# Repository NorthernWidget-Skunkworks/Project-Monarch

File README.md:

# Project-Monarch
Designs for a small scale and low cost pyronometer operating in both the short wave and long wave spectral regions

## Millable components

* [Pipe mount](https://easel.inventables.com/projects/cAirZefIUws53oghGYYopw). Accepts 1.25" to 3.25" innner diameter (ID) 1/4" (bolt diameter) U bolts. (1 1/8" U bolts are possible if you're willing to bend them.) Typical sizes available in the USA are 1.25", 1.5", 1.75", and 2".
* [Drilling jig](https://easel.inventables.com/projects/s-fOn9DWTmkeizO0vO8MGw) for Monarch box`

<br>
<br />This work is licensed under a <a rel="license" href="http://creativecommons.org/licenses/by-sa/4.0/">Creative Commons Attribution-ShareAlike 4.0 International License</a>.

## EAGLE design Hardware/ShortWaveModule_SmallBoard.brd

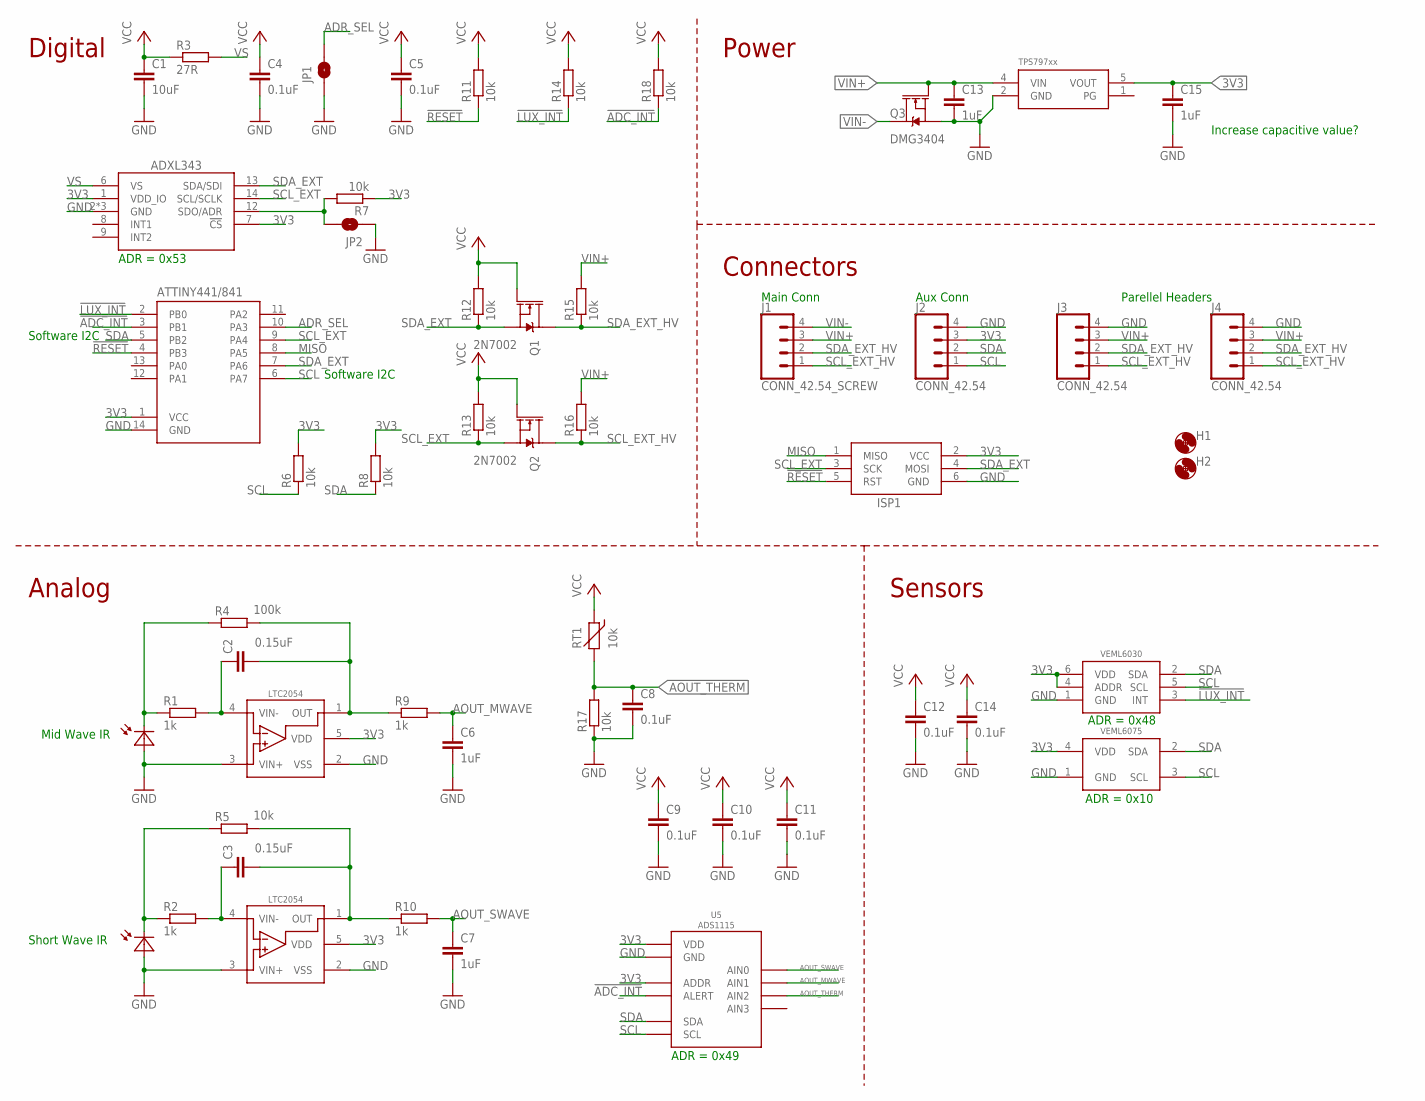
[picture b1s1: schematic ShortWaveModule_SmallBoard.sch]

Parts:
C1: 10uF; C0805
C2, C3: 0.15uF; C0603
C4, C5, C8, C9, C10, C11, C12, C14: 0.1uF; C0603
C6, C7, C13, C15: 1uF; C0603
D1: PHOTODIODESD003-151-001; D1206
D2: PHOTODIODEVEMD1060; D0805
H1, H2: MOUNTING_HOLE4_NP; 4_40
ISP1: AVRISP-6; AVRISP
J1: CONN_42.54_SCREW; 1X04_SCREW
J2, J3, J4: CONN_42.54; 1X04
JP1, JP2: JUMPER-SMT_2_NO_SILK; SMT-JUMPER_2_NO_SILK
Q1, Q2: 2N7002; SOT323
Q3: DMG3404; SOT23-3
R1, R2, R9, R10: 1k; R0603
R3: 27R; R0603
R4: 100k; R0603
R5, R6, R7, R8, R11, R12, R13, R14, R15, R16, R18: 10k; R0603
R17: 10k; R0603; MPN ERA-3AEB103V; DIGIKEY P10KDBCT-ND
RT1: 10k; R0603
U1: ADXL343; LGA-14
U2: ATTINY441/841841; SOIC_14
U3, U4: LTC2054; SOT23-5
U5: ADS1115; VSSOP_10
U6: TPS79733; DCK_R-PDSO-G5
U7: VEML6030
U8: VEML6075

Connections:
3V3: C1.1, C4.1, C5.1, C9.1, C10.1, C11.1, C12.1, C14.1, C15.1, ISP1.2 (VCC), J2.3, Q1.1 (G), Q2.1 (G), R3.1, R6.2, R7.1, R8.2, R11.2, R12.2, R13.2, R14.2, R18.2, RT1.1 (2), U1.1 (VDD_IO), U1.7 (!CS), U2.1 (VCC), U3.5 (VDD), U4.5 (VDD), U5.1 (ADDR), U5.8 (VDD), U6.5 (VOUT), U7.4 (ADDR), U7.6 (VDD), U8.4 (VDD)
!ADC_INT: R18.1, U2.3 (PB1), U5.2 (ALERT)
!LUX_INT: R14.1, U2.2 (PB0), U7.3 (INT)
!RESET: ISP1.5 (RST), R11.1, U2.4 (PB3)
ADR_SEL: JP1.2, U2.10 (PA3)
AOUT_MWAVE: C6.1, R9.2, U5.5 (AIN1)
AOUT_SWAVE: C7.1, R10.2, U5.4 (AIN0)
AOUT_THERM: C8.1, R17.2, RT1.2 (1), U5.6 (AIN2)
GND: C1.2, C4.2, C5.2, C6.2, C7.2, C8.2, C9.2, C10.2, C11.2, C12.2, C13.2, C14.2, C15.2, D1.A, D2.A, ISP1.6 (GND), J2.4, J3.4, J4.4, JP1.1, JP2.1, Q3.2 (S), R17.1, U1.2 (GND), U1.4 (GND), U1.5 (GND), U2.14 (GND), U3.2 (VSS), U3.3 (VIN+), U4.2 (VSS), U4.3 (VIN+), U5.3 (GND), U6.2 (GND), U7.1 (GND), U8.1 (GND)
MISO: ISP1.1 (MISO), U2.8 (PA5)
unnamed: JP2.2, R7.2, U1.12 (SDO/ADR)
unnamed: C3.1, R2.2, U4.4 (VIN-)
unnamed: D2.C, R2.1, R5.1
unnamed: D1.C, R1.1, R4.1
unnamed: C2.1, R1.2, U3.4 (VIN-)
unnamed: C2.2, R4.2, R9.1, U3.1 (OUT)
unnamed: C3.2, R5.2, R10.1, U4.1 (OUT)
SCL: J2.1, R6.1, U2.6 (PA7), U5.10 (SCL), U7.5 (SCL), U8.3 (SCL)
SCL_EXT: ISP1.3 (SCK), Q2.2 (S), R13.1, U1.14 (SCL/SCLK), U2.9 (PA4)
SCL_EXT_HV: J1.1, J3.1, J4.1, Q2.3 (D), R16.1
SDA: J2.2, R8.1, U2.5 (PB2), U5.9 (SDA), U7.2 (SDA), U8.2 (SDA)
SDA_EXT: ISP1.4 (MOSI), Q1.2 (S), R12.1, U1.13 (SDA/SDI), U2.7 (PA6)
SDA_EXT_HV: J1.2, J3.2, J4.2, Q1.3 (D), R15.1
VIN+: C13.1, J1.3, J3.3, J4.3, Q3.1 (G), R15.2, R16.2, U6.4 (VIN)
VIN-: J1.4, Q3.3 (D)
VS: R3.2, U1.6 (VS)

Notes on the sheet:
Software I2C
ADR = 0x48
ADR = 0x10
ADR = 0x49
Increase capacitive value?
Digital
Sensors
Power
Analog
Short Wave IR
Mid Wave IR
Connectors
Main Conn
Aux Conn
Parellel Headers
ADR = 0x53

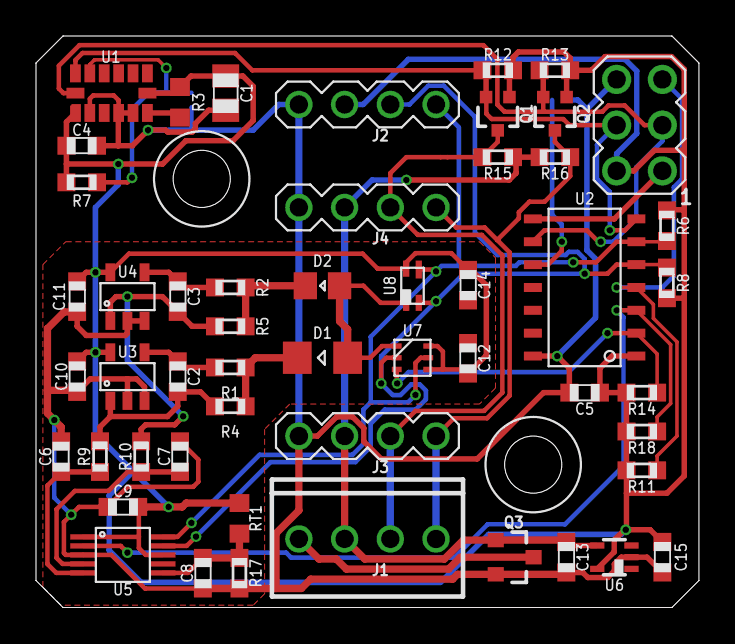
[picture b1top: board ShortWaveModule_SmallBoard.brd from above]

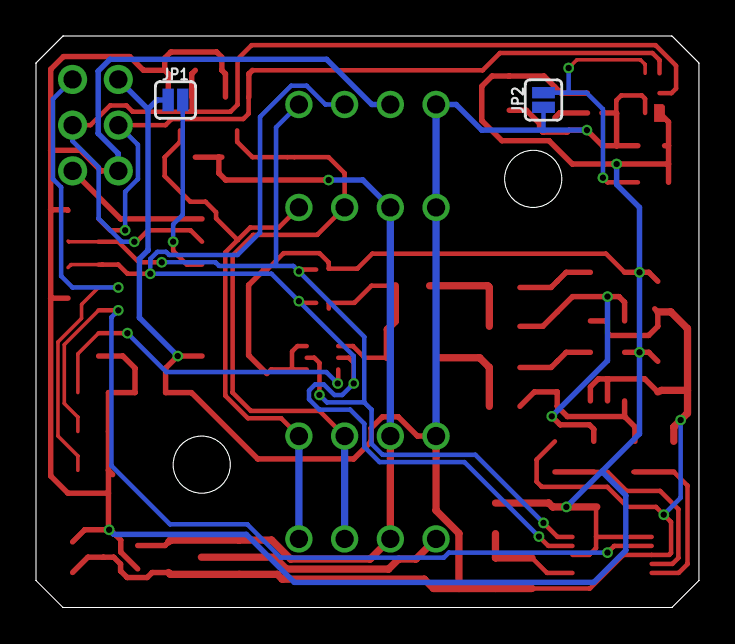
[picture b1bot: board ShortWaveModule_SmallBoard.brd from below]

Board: 2 copper layers, 36.8 x 31.8 mm, 56 parts (2 on the bottom side), 26 nets.

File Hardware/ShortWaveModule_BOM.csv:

"Qty","Value","Device","Package","Parts","Description","DIGIKEY","DISP","MF","MPN","PROD_ID","VALUE","VALUE_PART",
"2","","MOUNTING_HOLE4_NP","4_40","H1, H2","Genaric Mechanical Mounting Hole","","","","","","","",
"2","0.15uF","C-EU0.15UFC0603","C0603","C2, C3","CAPACITOR, European symbol","732-7990-1-ND","","Wurth","885012206072","","","",
"8","0.1uF","C-EU0.1UFC0603","C0603","C4, C5, C8, C9, C10, C11, C12, C14","CAPACITOR, European symbol","490-6051-1-ND","","Murata","GCM188R71E104KA57D","","","",
"1","100k","R-EU_P100KR0603","R0603","R4","RESISTOR, European symbol","P100KDBCT-ND","","Panasonic","ERA-3AEB104V","","","100k",
"10","10k","R-EU_10KR0603","R0603","R6, R7, R8, R11, R12, R13, R14, R15, R16, R18","RESISTOR, European symbol","P10.0KHCT-ND","","Panasonic","ERJ-3EKF1002V","","","10k",
"1","10k","R-EU_P10KR0603","R0603","R17","RESISTOR, European symbol","P10KDBCT-ND","","Panasonic ","ERA-3AEB103V","","","10k",
"1","10k","R-EU_P10KR0603","R0603","R5","RESISTOR, European symbol","P10KDBCT-ND","","Panasonic","ERA-3AEB103V","","","10k",
"1","10k","THERMISTOR10K","R0603","RT1","Thermistor","490-16279-1-ND","","Murata","NCU18XH103F60RB","","","",
"1","10uF","C-EU10UFC0805","C0805","C1","CAPACITOR, European symbol","490-6473-6-ND","","Murata","GRM21BR61C106KE15K","","","",
"4","1k","R-EU_P1KR0603","R0603","R1, R2, R9, R10","RESISTOR, European symbol","P1.0KDBCT-ND","","Panasonic","ERA-3AEB102V","","","1k",
"4","1uF","C-EU1UFC0603","C0603","C6, C7, C13, C15","CAPACITOR, European symbol","1276-6524-1-ND","","Samsung","1276-6524-1-ND","","","",
"1","27R","R-EU_27R0603","R0603","R3","RESISTOR, European symbol","311-27.0HRCT-ND","","Yageo","RC0603FR-0727RL","","","27",
"2","2N7002","MOSFET-NCH-2N7002PW","SOT323","Q1, Q2","N-channel MOSFETs","2N7002W-FDICT-ND","","Diodes Incorporated","2N7002W-7-F","TRANS-11151","2N7002","",
"1","ADS1115","ADS1115","VSSOP_10","U5","ADS1115 - Sigma Delta ADC","296-38849-1-ND","","TI","ADS1115IDGSR","","","",
"1","ADXL343","ADXL343","LGA-14","U1","ADXL343 - Digital Accelerometer(I2C/SPI)","ADXL343BCCZ-ND","","Analog Devices","ADXL343BCCZ","","","",
"1","ATTINY441/841841","ATTINY441/841841","SOIC_14","U2","ATTINY441, ATTINY841 8 bit MCU, 4/8k flash, 256/512B SRAM","ATTINY841-SSU-ND","","Atmel","ATTINY841-SSU","","","",
"1","AVRISP-6","AVRISP-6","AVRISP","ISP1","AVR ISP HEADER","","","","","","","",
"3","CONN_42.54","CONN_42.54","1X04","J2, J3, J4","Genaric 4 pin connector","","","","","","","",
"1","CONN_42.54_SCREW","CONN_42.54_SCREW","1X04_SCREW","J1","Genaric 4 pin connector","ED10563-ND","","On Shore","OSTVN04A150","","","",
"1","DMG3404","MOSFET-NCH-DMG3404L","SOT23-3","Q3","N-channel MOSFETs","DMG3404L-7DICT-ND","","Diodes Incorporated","DMG3404L-7","","DMG3404","",
"2","JUMPER-SMT_2_NO_SILK","JUMPER-SMT_2_NO_SILK","SMT-JUMPER_2_NO_SILK","JP1, JP2","Normally open jumper","","","","","","","",
"2","LTC2054","LTC2054","SOT23-5","U3, U4","LTC2054 -Single Micropower Zero Drift Op-Amp","LTC2054HS5#TRMPBFCT-ND","LTC2054","LT","LTC2054HS5#TRMPBF","","","",
"1","PHOTODIODESD003-151-001","PHOTODIODESD003-151-001","D1206","D1","Photodiode","SD003-151-001CT-ND","","Luna Opto","SD003-151-001","","","",
"1","PHOTODIODEVEMD1060","PHOTODIODEVEMD1060","D0805","D2","Photodiode","VEMD1060X01CT-ND ","","Vishay","VEMD1060X01","","","",
"1","TPS79733","TPS79733","DCK_R-PDSO-G5","U6","TPS797xx, Ultra low power linear voltage regulator, fixed voltages of 1.8v, 3v, 3.3v","296-11990-1-ND","","TI","TPS79733DCKR","","","",
"1","VEML6030","VEML6030","VEML6030","U7","VEML6030 - Ambient Light Sensor with I2C Interface","VEML6030-GS15CT-ND","","Vishay","VEML6030-GS15","","","",
"1","VEML6075","VEML6075","VEML6075","U8","VEML6075 - UVA and UVB Light Sensor with I2C Interface","VEML6075CT-ND","","Vishay","VEML6075","","","",

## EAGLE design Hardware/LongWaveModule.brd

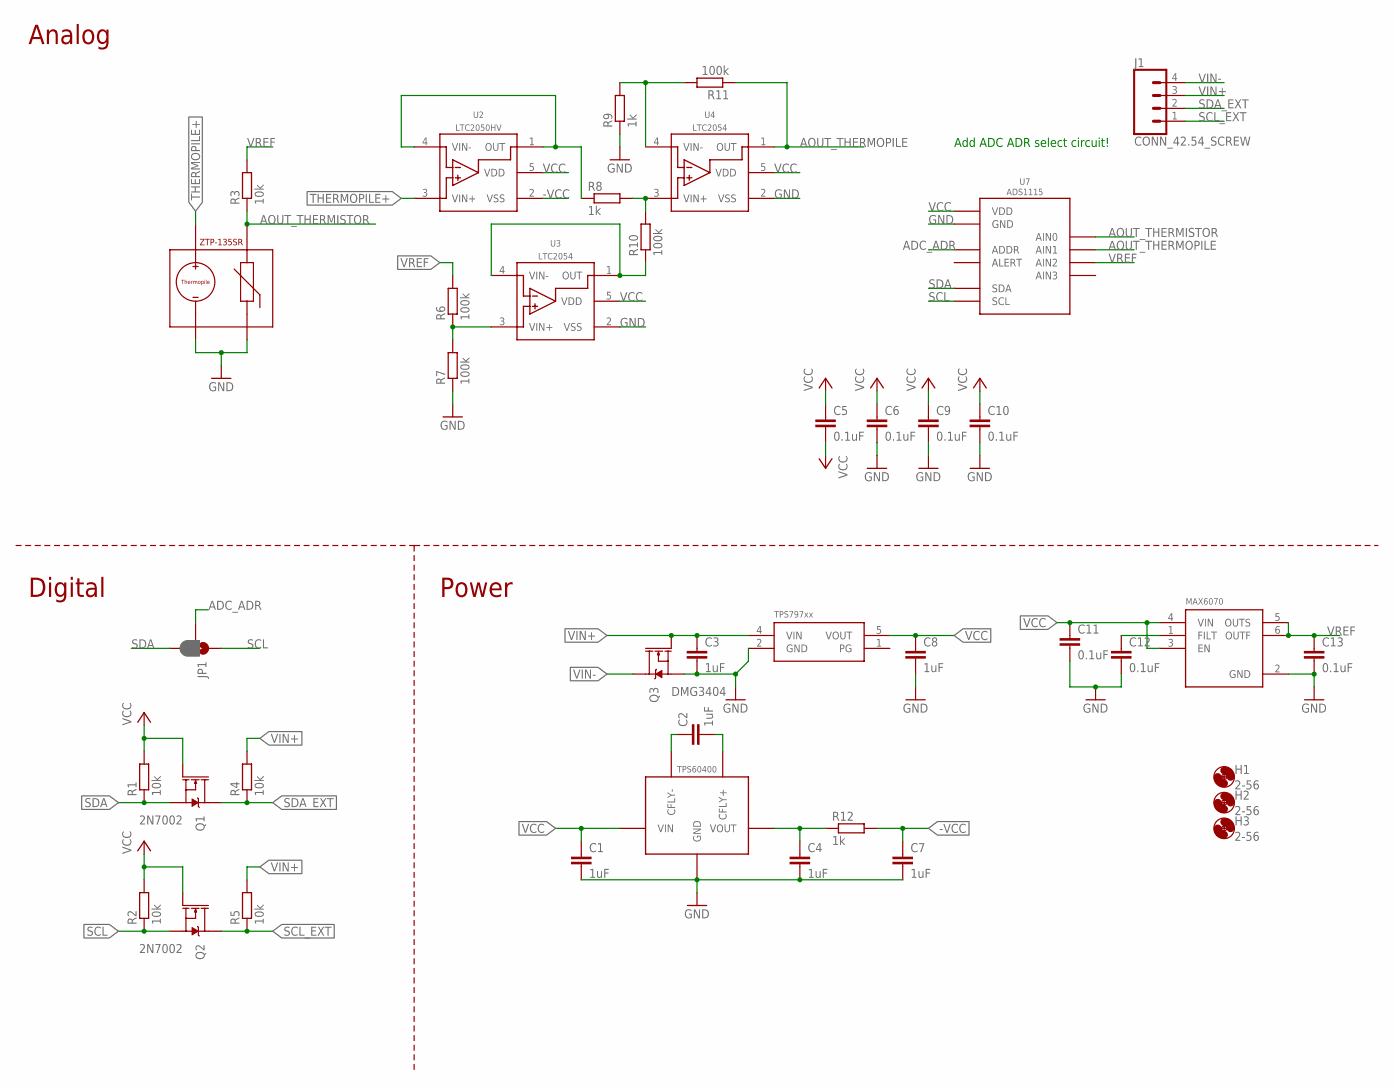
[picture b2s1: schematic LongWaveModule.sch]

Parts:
C1, C2, C3, C4, C7, C8: 1uF; C0603
C5, C6, C9, C10, C11, C12, C13: 0.1uF; C0603
H1, H2, H3: 2-56; 2_56
J1: CONN_42.54_SCREW; 1X04_SCREW
JP1: JUMPER-SMT_3_1-NC_PASTE_SILK; SMT-JUMPER_3_1-NC_PASTE_SILK
Q1, Q2: 2N7002; SOT323
Q3: DMG3404; SOT23-3
R1, R2, R3, R4, R5: 10k; R0603
R6, R7, R10, R11: 100k; R0603
R8, R9, R12: 1k; R0603
U1: STP-135SR; TO-46
U2: LTC2050HV; SOT23-5
U3, U4: LTC2054; SOT23-5
U5: TPS60403; SOT23-5
U6: TPS79733; DCK_R-PDSO-G5
U7: ADS1115; VSSOP_10
U8: MAX6070AAUT18; SOT23-6L

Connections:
-VCC: C5.2, C7.1, R12.2, U2.2 (VSS)
ADC_ADR: JP1.2, U7.1 (ADDR)
AOUT_THERMISTOR: R3.1, U1.THERMISTOR+, U7.4 (AIN0)
AOUT_THERMOPILE: R11.1, U4.1 (OUT), U7.5 (AIN1)
GND: C1.2, C3.2, C4.2, C6.2, C7.2, C8.2, C9.2, C10.2, C11.2, C12.2, C13.2, Q3.2 (S), R7.1, R9.1, U1.THERMISTOR_GND (THERMISTOR-), U1.THERMOPILE_GND (THEMROPILE-), U3.2 (VSS), U4.2 (VSS), U5.4 (GND), U6.2 (GND), U7.3 (GND), U8.2 (GND)
unnamed: R8.1, U2.1 (OUT), U2.4 (VIN-)
unnamed: R8.2, R10.2, U4.3 (VIN+)
unnamed: R9.2, R11.2, U4.4 (VIN-)
unnamed: R10.1, U3.1 (OUT), U3.4 (VIN-)
unnamed: R6.1, R7.2, U3.3 (VIN+)
unnamed: C12.1, U8.1 (FILT)
unnamed: C2.1, U5.3 (CFLY-)
unnamed: C2.2, U5.5 (CFLY+)
unnamed: C4.1, R12.1, U5.1 (VOUT)
SCL: JP1.1, Q2.2 (S), R2.1, U7.10 (SCL)
SCL_EXT: J1.1, Q2.3 (D), R5.1
SDA: JP1.3, Q1.2 (S), R1.1, U7.9 (SDA)
SDA_EXT: J1.2, Q1.3 (D), R4.1
THERMOPILE+: U1.THERMOPILE+, U2.3 (VIN+)
VCC: C1.1, C5.1, C6.1, C8.1, C9.1, C10.1, C11.1, Q1.1 (G), Q2.1 (G), R1.2, R2.2, U2.5 (VDD), U3.5 (VDD), U4.5 (VDD), U5.2 (VIN), U6.5 (VOUT), U7.8 (VDD), U8.3 (EN), U8.4 (VIN)
VIN+: C3.1, J1.3, Q3.1 (G), R4.2, R5.2, U6.4 (VIN)
VIN-: J1.4, Q3.3 (D)
VREF: C13.1, R3.2, R6.2, U7.6 (AIN2), U8.5 (OUTS), U8.6 (OUTF)

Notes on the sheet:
Add ADC ADR select circuit!
Analog
Digital
Power

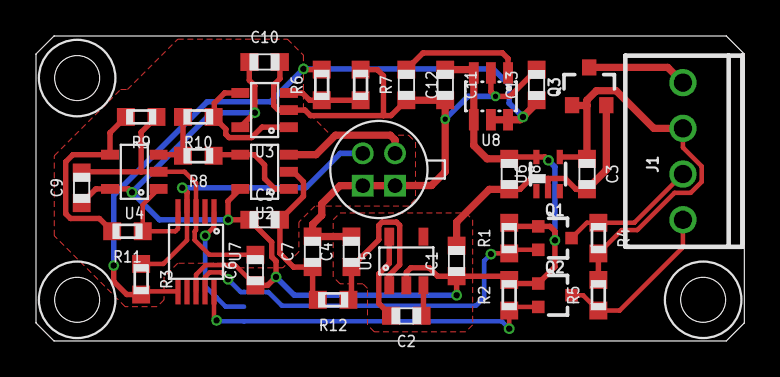
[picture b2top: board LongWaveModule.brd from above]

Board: 2 copper layers, 39.4 x 16.9 mm, 41 parts (1 on the bottom side), 23 nets.

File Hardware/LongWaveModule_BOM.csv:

"Qty","Value","Device","Package","Parts","Description","DIGIKEY","DISP","MF","MPN","PROD_ID","VALUE","VALUE_PART",
"7","0.1uF","C-EU0.1UFC0603","C0603","C5, C6, C9, C10, C11, C12, C13","CAPACITOR, European symbol","490-6051-1-ND","","Murata","GCM188R71E104KA57D","","","",
"4","100k","R-EU_P100KR0603","R0603","R6, R7, R10, R11","RESISTOR, European symbol","P100KDBCT-ND","","Panasonic","ERA-3AEB104V","","","100k",
"4","10k","R-EU_10KR0603","R0603","R1, R2, R4, R5","RESISTOR, European symbol","P10.0KHCT-ND","","Panasonic","ERJ-3EKF1002V","","","10k",
"1","10k","R-EU_P10KR0603","R0603","R3","RESISTOR, European symbol","P10KDBCT-ND","","Panasonic","ERA-3AEB103V","","","10k",
"1","1k","R-EU_1KR0603","R0603","R12","RESISTOR, European symbol","311-1KLDCT-ND","","Yageo","AC0603FR-071KL","","","1k",
"2","1k","R-EU_P1KR0603","R0603","R8, R9","RESISTOR, European symbol","P1.0KDBCT-ND","","Panasonic","ERA-3AEB102V","","","1k",
"6","1uF","C-EU1UFC0603","C0603","C1, C2, C3, C4, C7, C8","CAPACITOR, European symbol","1276-6524-1-ND","","Samsung","1276-6524-1-ND","","","",
"3","2-56","MOUNTING_HOLE2_NP","2_56","H1, H2, H3","Genaric Mechanical Mounting Hole","","","","","","","",
"2","2N7002","MOSFET-NCH-2N7002PW","SOT323","Q1, Q2","N-channel MOSFETs","2N7002W-FDICT-ND","","Diodes Incorporated","2N7002W-7-F","TRANS-11151","2N7002","",
"1","ADS1115","ADS1115","VSSOP_10","U7","ADS1115 - Sigma Delta ADC","296-38849-1-ND","","TI","ADS1115IDGSR","","","",
"1","CONN_42.54_SCREW","CONN_42.54_SCREW","1X04_SCREW","J1","Genaric 4 pin connector","ED10563-ND","","On Shore","OSTVN04A150","","","",
"1","DMG3404","MOSFET-NCH-DMG3404L","SOT23-3","Q3","N-channel MOSFETs","DMG3404L-7DICT-ND","","Diodes Incorporated","DMG3404L-7","","DMG3404","",
"1","JUMPER-SMT_3_1-NC_PASTE_SILK","JUMPER-SMT_3_1-NC_PASTE_SILK","SMT-JUMPER_3_1-NC_PASTE_SILK","JP1","Normally closed solder jumper (1 of 2 connections)","","","","","","","",
"1","LTC2050HV","LTC2050HV","SOT23-5","U2","LTC2050 -Single Micropower Zero Drift Op-Amp","LTC2050HVIS5#TRPBFCT-ND","LTC2050HV","LT","LTC2050HVIS5#TRPBF","","","",
"2","LTC2054","LTC2054","SOT23-5","U3, U4","LTC2054 -Single Micropower Zero Drift Op-Amp","LTC2054HS5#TRMPBFCT-ND","LTC2054","LT","LTC2054HS5#TRMPBF","","","",
"1","MAX6070AAUT18","MAX6070AAUT18","SOT23-6L","U8","MAX6070 Low Noise high precision voltage referance","MAX6070BAUT18+TCT-ND","","Maxim","MAX6070BAUT18+T","","","",
"1","STP-135SR","STP-135SR","TO-46","U1","ZTP-135SR - Thermopile Temp Sensor with integrated thermistor","235-1330-ND","","Amphenol","ZTP-135SR","","","",
"1","TPS60403","TPS60403","SOT23-5","U5","TPS6040x - Unregulated Charge Pump Voltage Inverter","296-27005-1-ND","","TI","TPS60403DBVR","","","",
"1","TPS79733","TPS79733","DCK_R-PDSO-G5","U6","TPS797xx, Ultra low power linear voltage regulator, fixed voltages of 1.8v, 3v, 3.3v","296-11990-1-ND","","TI","TPS79733DCKR","","","",

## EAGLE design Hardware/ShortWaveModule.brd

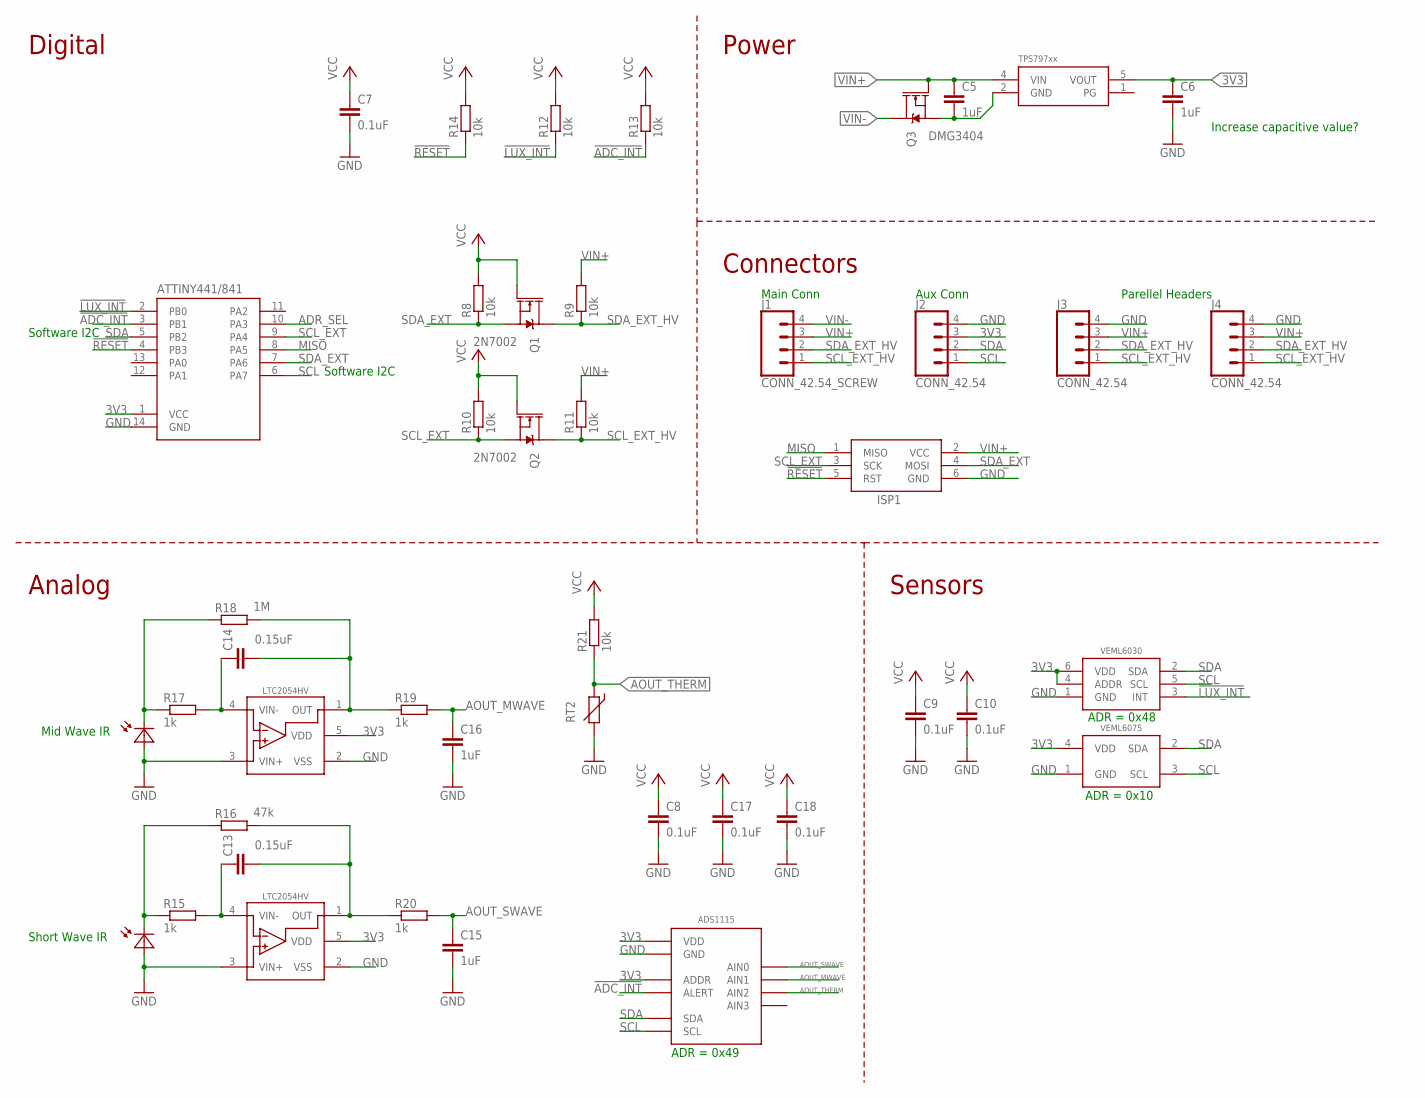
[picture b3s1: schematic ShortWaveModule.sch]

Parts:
ADS1115: ADS1115; VSSOP_10
C5, C6, C15, C16: 1uF; C0603
C7, C8, C9, C10, C17, C18: 0.1uF; C0603
C13, C14: 0.15uF; C0603
ISP1: AVRISP-6; AVRISP
J1: CONN_42.54_SCREW; 1X04_SCREW
J2, J3, J4: CONN_42.54; 1X04
Q1, Q2: 2N7002; SOT323
Q3: DMG3404; SOT23-3
R8, R9, R10, R11, R12, R13, R14, R21: 10k; R0603
R15, R17, R19, R20: 1k; R0603
R16: 47k; R0603
R18: 1M; R0603
RT2: THERMISTOR10K; R0603
U$1: ATTINY441/841841; SOIC_14
U$2: VEML6030
U$3: VEML6075
U$5: TPS79733; DCK_R-PDSO-G5
U$9: PHOTODIODEMTD5010W; TO-18
U$10: PHOTODIODESD003-151-001; D1206
U$11, U$12: LTC2054HV; SOT23-5

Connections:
3V3: ADS1115.1 (ADDR), ADS1115.8 (VDD), C6.1, C7.1, C8.1, C9.1, C10.1, C17.1, C18.1, J2.3, Q1.1 (G), Q2.1 (G), R8.2, R10.2, R12.2, R13.2, R14.2, R21.2, U$1.1 (VCC), U$2.4 (ADDR), U$2.6 (VDD), U$3.4 (VDD), U$5.5 (VOUT), U$11.5 (VDD), U$12.5 (VDD)
!ADC_INT: ADS1115.2 (ALERT), R13.1, U$1.3 (PB1)
!LUX_INT: R12.1, U$1.2 (PB0), U$2.3 (INT)
!RESET: ISP1.5 (RST), R14.1, U$1.4 (PB3)
ADR_SEL: U$1.10 (PA3)
AOUT_MWAVE: ADS1115.5 (AIN1), C14.2, R18.2, R19.1, U$11.1 (OUT)
AOUT_SWAVE: ADS1115.4 (AIN0), C13.2, R16.2, R20.1, U$12.1 (OUT)
AOUT_THERM: ADS1115.6 (AIN2), R21.1, RT2.1
GND: ADS1115.3 (GND), C6.2, C7.2, C8.2, C9.2, C10.2, C15.2, C16.2, C17.2, C18.2, ISP1.6 (GND), J2.4, J3.4, J4.4, RT2.2, U$1.14 (GND), U$2.1 (GND), U$3.1 (GND), U$9.ANODE (A), U$10.A, U$11.2 (VSS), U$11.3 (VIN+), U$12.2 (VSS), U$12.3 (VIN+)
MISO: ISP1.1 (MISO), U$1.8 (PA5)
unnamed: C5.2, Q3.2 (S), U$5.2 (GND)
unnamed: C13.1, R15.2, U$12.4 (VIN-)
unnamed: R15.1, R16.1, U$9.CATHODE (C)
unnamed: R17.1, R18.1, U$10.C
unnamed: C14.1, R17.2, U$11.4 (VIN-)
unnamed: C16.1, R19.2
unnamed: C15.1, R20.2
SCL: ADS1115.10 (SCL), J2.1, U$1.6 (PA7), U$2.5 (SCL), U$3.3 (SCL)
SCL_EXT: ISP1.3 (SCK), Q2.2 (S), R10.1, U$1.9 (PA4)
SCL_EXT_HV: J1.1, J3.1, J4.1, Q2.3 (D), R11.1
SDA: ADS1115.9 (SDA), J2.2, U$1.5 (PB2), U$2.2 (SDA), U$3.2 (SDA)
SDA_EXT: ISP1.4 (MOSI), Q1.2 (S), R8.1, U$1.7 (PA6)
SDA_EXT_HV: J1.2, J3.2, J4.2, Q1.3 (D), R9.1
VIN+: C5.1, ISP1.2 (VCC), J1.3, J3.3, J4.3, Q3.1 (G), R9.2, R11.2, U$5.4 (VIN)
VIN-: J1.4, Q3.3 (D)

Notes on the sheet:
Software I2C
ADR = 0x48
ADR = 0x10
ADR = 0x49
Increase capacitive value?
Digital
Sensors
Power
Analog
Short Wave IR
Mid Wave IR
Connectors
Main Conn
Aux Conn
Parellel Headers

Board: 2 copper layers, 44 parts (0 on the bottom side), 24 nets, no tracks yet.

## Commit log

2018-06-05 Rebuild repo
    Previous repo was borked due to inclusion of large peripheral files from LTSpice simulations, repo is now being rebuild with changes to gitignore in order to prevent issues like this in the future
2018-06-05 Made fixes to #2, #3, #4
    Fixed the silk screen numbering issue, fixed pinout of thermopile, connected voltage ref pin
2018-06-07 Added sub-alpha firmware
    I2C firmware used for translating I2C commands and readdressing (currently not functional), driver firmware is used as a true sensor interface to read from sub-slaves and populate registers (currentl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
2018-06-08 Improved driver files, and demo file
    Driver file in BETA, demo file still in ALPHA
2018-06-12 Updated to driver firmware and demo interface
    Initial design of driver firmware nearly completed, basics of demo interface complete, polishing and boilerplate required
2018-06-13 Firmware and demo interface updated
    Driver firmware and DysonReadDemo ready for full scale testing
2018-06-13 Added accelerometer to demo
2018-06-19 Improved firmware to include auto ranging
    Also added logging software ALPHA revision
2018-06-22 Added testing data logging script
2018-06-22 Added data and matlab plotting function
    Pyro17 was taken on cloudy day, pyro18 was taken in full sun
2018-06-27 Added pullups to shortwave module
    Added pullups to onboard I2C on shortwave module, still need to fix silk screen and update parts before ready to ship
2018-06-28 Updated parts and BOM
2018-06-28 Updated part info, license and BOM
2018-06-28 CC-BY-SA
2018-06-28 Generated gerbers for Mrk 0.1
    Added Gerbers for Mrk 0.1 revision, fixed silk screen issues, added pullup resistors for on board I2C on shortwave module, and changed amplifiers on longwave module (eliminated use of LTC2054HV, and 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
2018-07-10 Added mechanical parts and updated gerbers and ref designators
    Updated gerbers for long wave and fixed reference designators for short wave
2018-07-17 Added solder stencil DXF
2018-07-21 Added pipe mount assembly
2018-11-09 Added pin descriptors for Dyson v0.1
2018-11-09 Updated SW firmware, fixed ADR issue
    Updated Dyson shortwave firmware to fix alternative ADR setting issue. Also removed some stale debug statements and changed default flag to log when power is first applied to device in order to work 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
2018-11-09 Updated case mount to allow for pins to not clash
    added cutout to allow for clearance of backside of pins
2018-11-09 Updated plotting
2018-11-09 Added cutouts in mount
    Added cutouts for ICSP headers to allow board to lay flat on mount
2018-11-27 Added response curves for LW
    Added response curves for longwave sensor, and fitting info for thermistor on LW
2018-11-27 Added .dmp to gitignore
2018-11-29 Added mechanical parts
    Added placement guides and drill guide
2018-11-29 Added mechanical designs and reg map
    Added new mechanical designs along with a preliminary register map, continued expansion to come
2018-11-30 Added support for control register
    Added support for control register, including ready flag, variable update rate, manual auto range (and ability to turn off automatic auto ranging)
2018-12-01 Updated firmware
    Fixed update timing issue, need to remove digital pin debug statements!
2018-12-06 Changed busy flag structure
    Changed the structure of the busy flag to reduce the time the system is labeled as "busy" to just the time when actual registers are being updated. Need to remove bit flip debug statements!
2018-12-12 Added SW mount w/desiccant holders
    Added a new version of the board holder for the short wave unit, with spaces for holding desiccant that will not allow it to move around in the box and cause problems
2018-12-13 Added SW mount w/desiccant holders
2018-12-15 Added pipe mount cutout shape
2019-01-14 Fixed crash in Board Mount
    The pins of the bottom header would crash with the body of the BoardCaseMount, this was fixed with an cutout in `BoardCaseMount_DesicantHolder.SLDPRT`. Also updated`.stl` and generated bulk GCode to 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
2019-01-14 Removed GCode
    GCode should be kept locally only, has no reason to be in public general repo
2019-01-28 Added version number to firmware
2019-02-21 Added Kipp and Zonen test script
    Added logging script for use with Margay that measures data from Dyson SW and Kipp and Zonen CMP3. Need to fix address error
2019-05-21 Added experimental high speed/low power firmware
2019-06-24 comma data separator
2019-06-24 String typing, Margay1.0, Correct I2C addr
2020-05-01 GNU GPL v3 for code products (software, firmware, etc.)
2020-05-27 Design files
2020-05-27 Easel pipe mount
2020-05-27 Millable components and U bolt sizes
2021-11-02 Dyson-->Monarch, aside from Eagle files & co
2021-11-03 Dyson --> Monarch in sch and on silk
2021-11-03 Zenodo DOI badge

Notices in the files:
parts and their libraries:
SparkFun-Jumpers: Licensing: Creative Commons ShareAlike 4.0 International - https://creativecommons.org/licenses/by-sa/4.0
bschulz: This work is licensed under the Creative Commons Attribution-ShareAlike 4.0
